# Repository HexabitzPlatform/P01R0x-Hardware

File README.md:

# P01R0x-Hardware
Hexabitz RGB LED Module Hardware Design

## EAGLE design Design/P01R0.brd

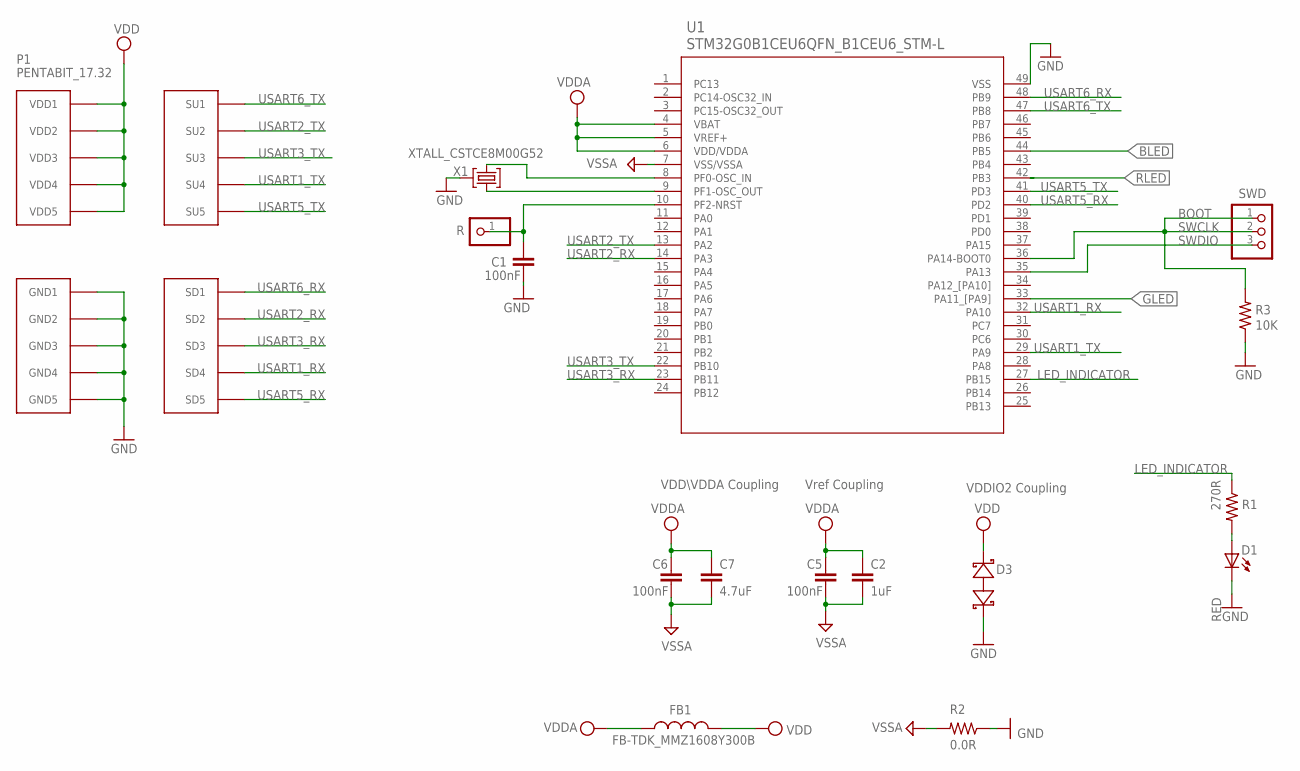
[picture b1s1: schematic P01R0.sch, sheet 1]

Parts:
C1, C5, C6: 100nF; C-0603
C2: 1uF; C-0805
C7: 4.7uF; C-0805
D1: RED; VLMS1300-GS08; MPN VLMS1300-GS08
D3: BOURNS_CDSOD323-T03SCBOURNS_CDSOD323-T03SC_0_0; BOURNS_CDSOD323-T03SC_0
FB1: FB-TDK_MMZ1608Y300B; FB-0603; MPN MMZ1608Y300B
P1: PENTABIT_17.32
R: R; 1X01
R1: 270R; R-0603
R2: 0.0R; R-0603; MPN RC0603JR-070RL
R3: 10K; R-0603
SWD: PINHD-1X3; 1X03
U1: STM32G0B1CEU6QFN_B1CEU6_STM-L; QFN_B1CEU6_STM-L
X1: XTALL_CSTCE8M00G52

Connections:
BLED: U1.44 (PB5); also elsewhere on the board
GLED: U1.33 (PA11_[PA9]); also elsewhere on the board
GND: C1.2, D1.C, D3.1 (A), P1.PAD_PD6 (GND1), P1.PAD_PD7 (GND2), P1.PAD_PD8 (GND3), P1.PAD_PD9 (GND4), P1.PAD_PD10 (GND5), R2.1, R3.1, U1.49 (VSS), X1.P$2 (2); also elsewhere on the board
LED_INDICATOR: R1.1, U1.27 (PB15)
unnamed: D1.A, R1.2
OSC_IN: U1.8 (PF0-OSC_IN), X1.P$3 (3)
OSC_OUT: U1.9 (PF1-OSC_OUT), X1.P$1 (1)
R: C1.1, R.1, U1.10 (PF2-NRST)
RLED: U1.42 (PB3); also elsewhere on the board
SWCLK: R3.2, SWD.1, SWD.2, U1.36 (PA14-BOOT0)
SWDIO: SWD.3, U1.35 (PA13)
USART1_RX: P1.PAD_PD4 (SD4), U1.32 (PA10)
USART1_TX: P1.PAD_PU4 (SU4), U1.29 (PA9)
USART2_RX: P1.PAD_PD2 (SD2), U1.14 (PA3)
USART2_TX: P1.PAD_PU2 (SU2), U1.13 (PA2)
USART3_RX: P1.PAD_PD3 (SD3), U1.23 (PB11)
USART3_TX: P1.PAD_PU3 (SU3), U1.22 (PB10)
USART5_RX: P1.PAD_PD5 (SD5), U1.40 (PD2)
USART5_TX: P1.PAD_PU5 (SU5), U1.41 (PD3)
USART6_RX: P1.PAD_PD1 (SD1), U1.48 (PB9)
USART6_TX: P1.PAD_PU1 (SU1), U1.47 (PB8)
VDD: D3.2 (C), FB1.2, P1.PAD_PU6 (VDD1), P1.PAD_PU7 (VDD2), P1.PAD_PU8 (VDD3), P1.PAD_PU9 (VDD4), P1.PAD_PU10 (VDD5); also elsewhere on the board
VDDA: C2.1, C5.1, C6.1, C7.1, FB1.1, U1.4 (VBAT), U1.5 (VREF+), U1.6 (VDD/VDDA)
VSSA: C2.2, C5.2, C6.2, C7.2, R2.2, U1.7 (VSS/VSSA)

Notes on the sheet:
Vref Coupling
VDDIO2 Coupling
VDD\VDDA Coupling
BOOT

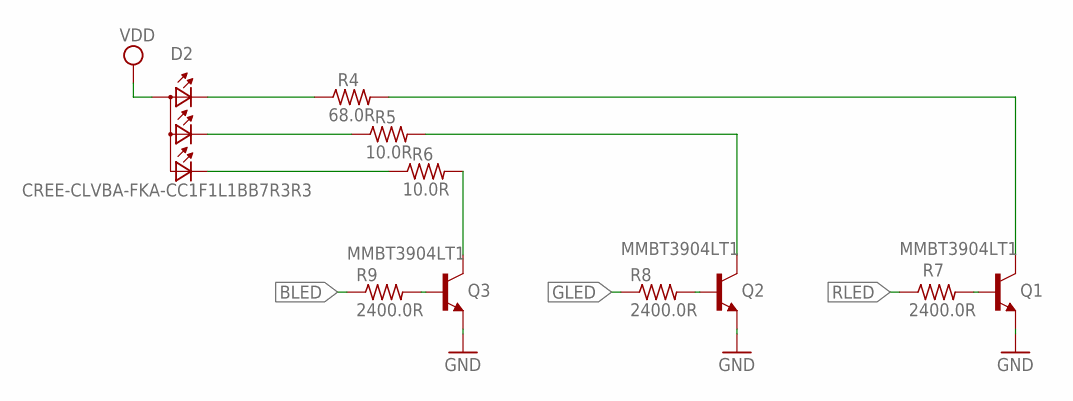
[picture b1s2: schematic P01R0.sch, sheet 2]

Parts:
D2: CREE-CLVBA-FKA-CC1F1L1BB7R3R3; PCB-1023943-1; MPN CLVBA-FKA-CC1F1L1BB7R3R3
Q1, Q2: MMBT3904LT1; VOLTAGE_RATING_DC 40.0V
Q3: MMBT3904LT1; VOLTAGE_RATING_DC 40.0V; MPN MMBT3904LT1G
R4: 68.0R; R-0603; TOLERANCE 1%; MPN CRCW060368R0FKEA
R5, R6: 10.0R; R-0603; TOLERANCE 1%; MPN CRCW060310R0FKEB
R7, R8, R9: 2400.0R; R-0603; TOLERANCE 5%; MPN CRCW06032K40JNEA
TRIMBLE-LOGO1: HEXA-LOGO

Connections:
BLED: R9.1; also elsewhere on the board
GLED: R8.1; also elsewhere on the board
GND: Q1.2 (E), Q2.2 (E), Q3.2 (E); also elsewhere on the board
KA_B: D2.P$3 (CBLUE), R6.1
KA_G: D2.P$4 (CGREEN), R5.1
KA_R: D2.P$1 (CRED), R4.1
unnamed: Q3.1 (B), R9.2
unnamed: Q2.1 (B), R8.2
unnamed: Q1.1 (B), R7.2
Q1C: Q1.3 (C), R4.2
Q2C: Q2.3 (C), R5.2
Q3C: Q3.3 (C), R6.2
RLED: R7.1; also elsewhere on the board
VDD: D2.P$2 (A2); also elsewhere on the board

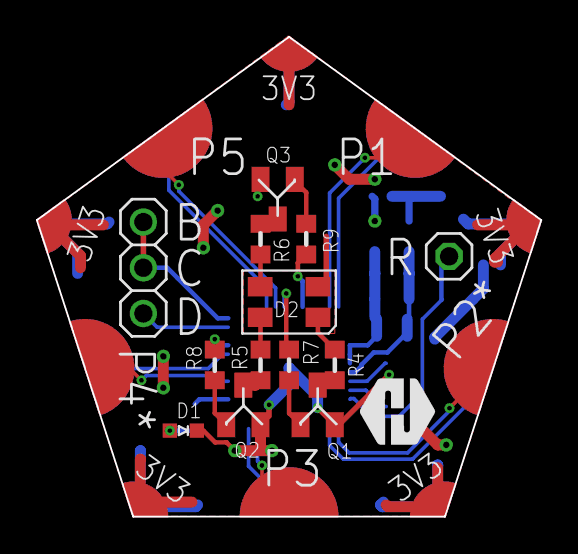
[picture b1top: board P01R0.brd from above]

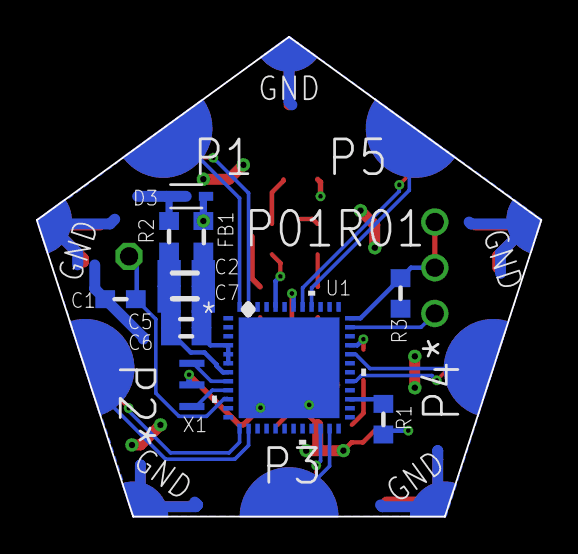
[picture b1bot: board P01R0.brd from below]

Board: 2 copper layers, 28.0 x 26.6 mm, 27 parts (12 on the bottom side), 33 nets.

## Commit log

2024-01-30 -Intial template
2024-01-30 -Editing the BOM
2024-02-25 -Changing the MCU to STM32G0B1CEU6N -Adding TVS 3.3V -Reviewed version , all finish
2024-04-02 Update the Logo
2024-07-14 -Add TVS diode -Change the MCU to STM32G0B1CEU6 -Activate the thermal option for the polygon -Improve the layout design for better appearence
2024-07-14 -Fix the BOM
2024-09-10 -Delete unnecessary files

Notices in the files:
parts and their libraries:
COPYRIGHT: Copyright (C) 2021 Ultra Librarian. All rights reserved.
